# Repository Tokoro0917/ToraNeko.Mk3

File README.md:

# ToraNeko.Mk3

マイクロマウス（ハーフサイズクラス）ToraNeko の3代目機体（Mk3）のソフトウェア・ハードウェア（回路）・機構設計をまとめて管理するリポジトリです。
KOGUMA（クラシックサイズ機）とは別系譜の機体です。前身の KOGUMA.Mk3 系リポジトリはソフトウェアのみを対象としていましたが、本リポジトリでは
回路図・基板データ・配線資料なども含めて一元管理し、ソフトとハードの変更履歴を紐付けて追跡できるようにします。

ロボットの詳細な概要・仕様は [docs/overview.md](./docs/overview.md) を参照してください。
機体で選べるモードの一覧は [software/main-controller/README.md の「モード一覧」](software/main-controller/README.md#モード一覧今のファームウェアで選べるもの) にあります。

## ディレクトリ構成

```
.
├── software/    # マイコン・PC側ソフトウェア一式
├── hardware/    # 回路図・基板データ（KiCadプロジェクト）・BOM
├── mechanical/  # 機構部品・3Dモデル・図面
└── docs/        # 配線図、仕様書、設計メモ、議事録などのドキュメント
```

各ディレクトリの詳細は、それぞれの README.md を参照してください。

## 設計データの管理方針

- 回路・基板設計は [KiCad](https://www.kicad.org/) を使用します。プロジェクト一式は `hardware/kicad/` 以下にサブシステムごとのディレクトリを作って格納します。
- ソフトウェアは `software/` 以下にサブシステム・マイコンボードごとのディレクトリを作って格納します。
- 既存の KOGUMA.Mk3 のソフトウェア資産は、必要になったタイミングで個別に移行するかを検討します（現時点では未移行）。

## ライセンス

このリポジトリは [MIT License](./LICENSE) の下で公開されます。

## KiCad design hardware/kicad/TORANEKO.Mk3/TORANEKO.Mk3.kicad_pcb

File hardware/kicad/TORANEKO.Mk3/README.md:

# TORANEKO.Mk3

ToraNeko.Mk3 のメイン基板（1枚基板・全機能統合、基板一体型シャーシ）のKiCadプロジェクトです。

KiCadプロジェクト本体（`TORANEKO.Mk3.kicad_pro` / `.kicad_sch` / `.kicad_pcb`）を作成済みです（現状は空、これから回路図を起こしていきます）。
このディレクトリには、実際に回路図を起こす前に固めておいた機能ブロック構成・ペリフェラル割り当て案・BOMドラフトも一緒に置いています。

## 機能ブロック

| ブロック | 内容 |
|---|---|
| MCU | STM32F411CEU6 |
| モータドライバ | MP6551 × 2（左モータ用・右モータ用） |
| モータ | NFP-D0812-1-3.7（ブラシ付きDC）× 2 |
| エンコーダ | AS5047P（磁気式）× 2、磁石は左右のタイヤの軸（3×6 平行ピン）に取り付け |
| IMU | LSM6DSRXTR |
| 壁センサ | 反射型IR。受光: LTR-209、発光: OSI5FU3A11C、LEDドライバ: **NCR321PAS**（定電流・PWM対応）。前方斜め左右2組・側面左右2組の計4組 |
| 吸引ファン | サクションファン × 1（型番未定）。NチャネルMOSFETによるローサイドPWM駆動 |
| 電源 | 2セルLiPo入力 → MCU/センサ用3.3V系（**LXDC55FAAA-203**）、モータドライバ（MP6551）はLiPo直結 |
| デバッグ/書き込み | STLINK-V3MODS（SWD＋仮想COMポート）。USBは使わない |
| クロック | HSE 10MHz（セラミック発振子 CSTNE10M0G52Z000R0）→ SYSCLK 100MHz |

## ペリフェラル割り当て案（STM32F411CEU6）

正確なピン番号はKiCadで回路図を起こす際にデータシート（UFQFPN48パッケージ）で確定してください。
ここではどのペリフェラルをどのブロックに割り当てるかの方針のみ示します。

- **SPIバス（IMU・エンコーダ用）**: LSM6DSRXTR、AS5047P × 2 は共通SPIバス上にCS（チップセレクト）を分けて接続する案。SPIバスを分割するかは配線の都合で判断。
- **PWM（モータ駆動用）**: MP6551 × 2 に対し、1モータあたり2本（IN1/IN2、もしくはPWM+DIR）を想定。TIM1などの高機能タイマーを優先的に割り当てる。
- **ADC（壁センサ用）**: LTR-209（受光）× 4組ぶんでADC 4チャンネル（PA3〜PA6）を使用。OSI5FU3A11C（発光）側は **NCR321PAS**（LED 1個につき1個）の VEN を GPIO 2本で2組ずつ駆動する（組A: PB0、組B: PA7）
- **PWM（吸引ファン用）**: MOSFETゲート駆動用に1チャンネル。モータ駆動用タイマーとは別チャンネルを割り当てる。
- **UART（ログ出力）**: USART1（PA9 TX / PA10 RX）を STLINK-V3MODS の仮想COMポートに接続する案。USBは使わないので PA11/PA12 は他用途に使える。
- **SWD**: STLINK-V3MODS での書き込み・デバッグ用に PA13（SWDIO）/ PA14（SWCLK）/ NRST を確保。SWO（PB3）は任意。

## 電源設計メモ

- 入力: 2セルLiPo（7.4V公称、満充電8.4V程度）
- MCU/センサ系: 3.3Vへ降圧、**LXDC55FAAA-203** を使用
- 壁センサLEDドライバ（NCR321PAS）: **3.3V系から給電（決定）**。センサ周りにバッテリ電圧（変動する電圧）を持ち込まないため。LED 1個につき NCR321PAS 1個、**ピーク約 155mA** のパルス点灯。回路は下記「壁センサ発光回路」を参照
- モータ系: LiPoをレギュレータを介さず**MP6551に直結**（MP6551の定格電圧範囲内であることを確認済みとして進める）
- 吸引ファン系: LiPoから供給、MOSFETでPWM制御（レギュレータを挟むかはファン選定後に確定）

## 壁センサ発光回路

LED 1個につき NCR321PAS 1個（×4組）。発光制御の GPIO は2本で、1本の GPIO で2個の VEN を同時に駆動する（組A: PB0 → IC3/D7 と IC8/D9、組B: PA7 → IC4/D8 と IC9/D10）。組み合わせは **組A = 左前向き＋右向き、組B = 右前向き＋左向き**。横向きの2組は光軸が機体中央で交差する（クロス配置）が、別の組なので同時には点かない。同時に点く2組は向きが反対なので干渉しにくい。ただし同じ組の2個は機体の同じ側に並ぶ（右向きは左側に付いて右を向くため）ので、LED からの光が隣の受光素子に直接入らないよう、センサホルダで遮光する。

2個同時点灯なのでピーク電流は約 310mA（155mA × 2）。大容量コンデンサの電圧降下も2倍になり、NCR321PAS の電圧余裕は最悪で 1.4V をわずかに下回る見込み。足りない場合は電流が少し下がる（暗くなる）だけなので、実測で確認する。

```
【電源部：4組で共通】

 +3V3 ──[FB1]──┬──────────┬───────────── 3V3_LED（LED1〜4のアノードへ）
 (MCU系)        │          │
            C1,C2 ═╧═      C3 ═╧═ 0.1µF
         47µF×2 │          │
                 GND        GND

【発光部：1組分（×4組）】

 3V3_LED
    │
    ▼  D1  OSI5FU3A11C（1: アノード、2: カソード）
    │
  ┌─┴──────────────── U1 NCR321PAS ──┐
  │  6: IOUT / 7: IOUT（裏面パッド）  │
  │  1: VEN ◄───────┬──────── GPIO（組A: PB0 / 組B: PA7、1本で2個の VEN を駆動）
  │                R2 100kΩ           │
  │                 │                 │
  │                GND                │
  │  2: REXT ──[R1 5.1Ω 1%]── GND     │
  │  5: GND ───────────────── GND     │
  │  3, 4, 8: N/C                     │
  └───────────────────────────────────┘
```

| 記号 | 部品 | 値 | 数 | 備考 |
|---|---|---|---|---|
| D1 | 赤外LED | OSI5FU3A11C | 4 | 940nm。IF=100mA で VF typ 1.35V / max 1.6V。パルス最大 1000mA（100µs, 1/100） |
| U1 | 定電流ドライバ | NCR321PAS | 4 | DFN2020D-6 |
| R1 | Rext | 5.1Ω 1% | 4 | 約 155mA（データシート Fig.16/17 の 4Ω≒190mA、6Ω≒135mA から 1/Rext で補間）。E96 の 4.99Ω なら約 160mA。センサごとに差し替え可能なよう 0603/0805 |
| R2 | VEN プルダウン | 100kΩ | 4 | リセット中（GPIO 入力状態）に LED が点かないようにする |
| FB1 | フェライトビーズ | 0603、定格 300mA 以上、DCR 0.1Ω 以下 | 1 | 0Ω でも可。MCU・ADC 側の 3.3V にパルス電流を流さないため |
| C1, C2 | バルクコンデンサ | 47µF 10V X5R 1206 | 2 | DC バイアス込みで実効 100µF 程度を確保。ドライバ直近 |
| C3 | デカップリング | 0.1µF | 1 | ドライバ直近。4組が離れる場合は各ドライバに追加 |

### 設計上の注意

- **VEN は GPIO から直結**（直列抵抗を入れない）。EN 電圧で出力電流が変わる（Fig.24）ため。VEN の絶対最大定格は 4.5V
- **NCR321PAS の裏面パッド（7ピン）は IOUT。GND ではない。** GND ベタにつなぐと LED が常時点灯になる。LED カソードと同じネットにし、放熱用に銅箔を確保する
- 電圧余裕（155mA 時の見積り）: 3.3V − C1,C2 電圧降下（約 31mV: 155mA × 20µs / 100µF）− FB1（約 16mV）− VF（推定 typ 1.65V / 最悪 1.8V）= **typ 約 1.6V / 最悪 約 1.45V**。NCR321PAS の最小オーバーヘッド 1.4V を満たす（180mA〔4.3Ω〕だと最悪で約 1.4V とぎりぎりになるため、安定性を優先して 5.1Ω とした）
  - このため **1回の点灯時間は 10〜20µs** を目安にする（ソフト側で調整）
  - 余裕が足りない場合は電流が設定値より下がる（暗くなる）だけで、壊れはしない。ただし明るさが温度で変わりやすくなる
- パルス電流のループ（C1,C2 → LED → U1 → R1 → GND → C1,C2）を小さくし、受光側・ADC 入力の近くを通さない
- 側面センサは壁が近く、受光側が飽和する可能性がある。実測で距離と AD 値の関係を確認し、必要ならセンサごとに Rext を変える（例: 側面は 9.1Ω≒100mA）

## 部品配置ガイド（DXF）

機体全体の STEP（`mechanical/exported/TORANEKO.Mk3_v36.step`）から、配置の目安になる DXF を生成したもの。KiCad の PCB エディタで「ファイル → インポート → グラフィック」から `User.Drawings` などのレイヤーに読み込み、ガイド内の基板外形（レイヤー `00_BOARD`）が既存の Edge.Cuts に重なるように置く。

### `配置ガイド_メイン基板.dxf`（上から見た図。`メイン基板外形.dxf` と同じ座標系）

| レイヤー | 内容 |
|---|---|
| `00_BOARD` | メイン基板外形（位置合わせ用） |
| `10_ENC_BOARD` | エンコーダ基板が立つ位置（6 × 0.6mm）と中心線 |
| `11_ENC_CHIP` | AS5047P の位置（エンコーダ基板の外側＝磁石側の面） |
| `12_MAGNET_AXIS` | 磁石（Φ3）と回転軸の線 |
| `20_CONTACT` | 基板面（z=0.65mm）で切った断面＝基板に接する部品の足元（モータマウント、センサホルダ、支柱、ホイール、41T ギア） |
| `30_OVERHANG` | 基板の上に浮いている部品の外形（破線）。ラベルの値は基板上面からの隙間＝その下に置ける部品の高さの上限 |

基板上面からの隙間（この高さ未満の部品なら下に置ける）:

| 部品 | 隙間 |
|---|---|
| モータ NFP-D0812 | 1.25mm |
| ベアリング LF-630 | 1.01mm |
| 吸引ファンモータ MK06-45 | 2.00mm |
| 平行ピン 3×6 / 磁石 | 3.11mm |
| ピニオン 11T | 3.36mm |
| 吸引ファンモータマウント | 4.98mm |

### エンコーダ基板の位置（KiCad 座標）

現在のメイン基板外形の取り込み位置（DXF 原点 → KiCad (96.5, 61.05)）で換算した値。

| | エンコーダ基板が立つ範囲 | 中心 | AS5047P（チップ）がある側 | 磁石 |
|---|---|---|---|---|
| 右（機体右、非ミラー側） | X 118.257〜118.857、Y 63.05〜69.05 | (118.557, 66.05) | +X 側（X 118.81〜120.00） | X 120.5〜121.5 |
| 左（機体左、ミラー側） | X 100.943〜101.543、Y 63.05〜69.05 | (101.243, 66.05) | −X 側（X 99.80〜100.99） | X 98.3〜99.3 |

- 磁石の回転軸は Y = 66.05、メイン基板上面から高さ 4.61mm
- エンコーダ基板は高さ 8.5mm、厚さ 0.6mm（STEP 上）。AS5047P と磁石の隙間は 0.5mm

### `配置ガイド_エンコーダ基板.dxf`（エンコーダ基板を磁石側から見た図。`エンコーダ外形.dxf` と同じ座標系）

- 上端（y = 0.513）がメイン基板にはんだ付けされる辺
- 磁石の軸（Φ1 の円）はメイン基板から 4.61mm。AS5047P はこの軸に中心を合わせ、フットプリントを 90° 回して置く（ピンの列が上下に来る向き）
- AS5047P のパッドから基板端までは、メイン基板側 0.94mm、反対側 0.21mm（反対側は製造ルールの最小クリアランスを要確認）
- `30_EDGE_PAD_ZONE`: メイン基板とはんだ付けするエッジパッドを置ける範囲。裏面（チップのない面）は幅いっぱいに 0.79mm、チップ面は同じ 0.79mm の帯か、左右の角（0.68 × 1.3mm）

## エンコーダ接続用フットプリント（`TORANEKO_Encoder.pretty/`）

エンコーダ基板（6 × 8.5 × 0.6mm）をメイン基板に垂直に立て、はんだで接続するためのフットプリント。左右のエンコーダ基板は同じ設計のまま使える（180° 回して置くだけ）。

| フットプリント | 使う部品 | 原点 | パッド |
|---|---|---|---|
| `TN_ENC_Edge` | エンコーダ基板側（U3, U5） | はんだ付けする辺の中央。+Y が基板の奥（メイン基板から離れる向き） | 1〜4（MOSI, MISO, SCK, CS）: 裏面、幅 0.9mm、ピッチ 1.4mm、辺から 0.2〜1.2mm。5〜6（VCC, GND）: チップ面、幅 2.0mm、辺から 0.2〜0.72mm（AS5047P のパッドと 0.2mm 以上離す） |
| `TN_ENC_Base` | メイン基板側（U4, U6） | エンコーダ基板が立つ位置の中央。−Y がチップ側 | 1〜4: 裏面側の列、5〜6: チップ側の列。エンコーダ基板の面（中心から ±0.3mm）から外へ 1.0mm |

- `TN_ENC_Edge` の `Dwgs.User` に、磁石の軸（辺から 4.613mm）と AS5047P の外形（5.0 × 4.4mm）を描いてある。AS5047P はその中心に合わせ、90° 回して置く
- `TN_ENC_Base` の置き方（回転は KiCad の角度）:

| | 位置 | 回転 |
|---|---|---|
| 右エンコーダ（U4 か U6、チップが +X 向き） | (118.557, 66.05) | 270° |
| 左エンコーダ（チップが −X 向き） | (101.243, 66.05) | 90° |

- エンコーダ基板は小さいため、基板端クリアランス（基板のセットアップ → 制約 → 銅箔から基板端）は **0.2mm** にする（0.5mm だと AS5047P のパッドとエッジパッドが違反になる。AS5047P のパッドは上端から 0.22mm）
- ライブラリの追加: 設定 → フットプリントライブラリの管理 → プロジェクト固有のライブラリ に `${KIPRJMOD}/TORANEKO_Encoder.pretty` を追加

## TODO

- [x] SPIバスの分割方針 → IMU は SPI1（PB3/4/5）、エンコーダは SPI2（PB13/14/15）に分割
- [x] モータPWM用タイマー・チャンネルの確定 → TIM4 CH1〜CH4（PB6〜PB9）
- [ ] NCR321PASの電流設定抵抗値の実測確認: **Rext = 5.1Ω（1%、約 155mA）** に決定。実機で電流・IOUT 電圧（1.2V 以上残っているか）・温度による AD 値の変化を確認
- [ ] NCR321PASの3.3V系での電圧マージン実測確認（155mA 時の見積りは typ 約1.6V / 最悪 約1.45V。OSI5FU3A11C の 155mA 時 VF はデータシートに記載がないため実測が必要）
- [ ] LXDC55FAAA-203 の出力電流に LED パルス分（最大約 155mA、同時点灯1個）の余裕があるか確認
- [ ] 吸引ファンの型番選定
- [ ] 吸引ファン用MOSFET・ゲート抵抗・フライホイールダイオードの選定
- [ ] 吸引ファンの電源系統（LiPo直結か別レギュレータか）の判断
- [x] 正式なピンアサイン表の作成 → `software/main-controller/PIN_REQUIREMENTS.md`（回路図 `9a54a18` から抽出）
- [ ] 各部品のシンボル・フットプリントをライブラリに追加し、回路図に配置

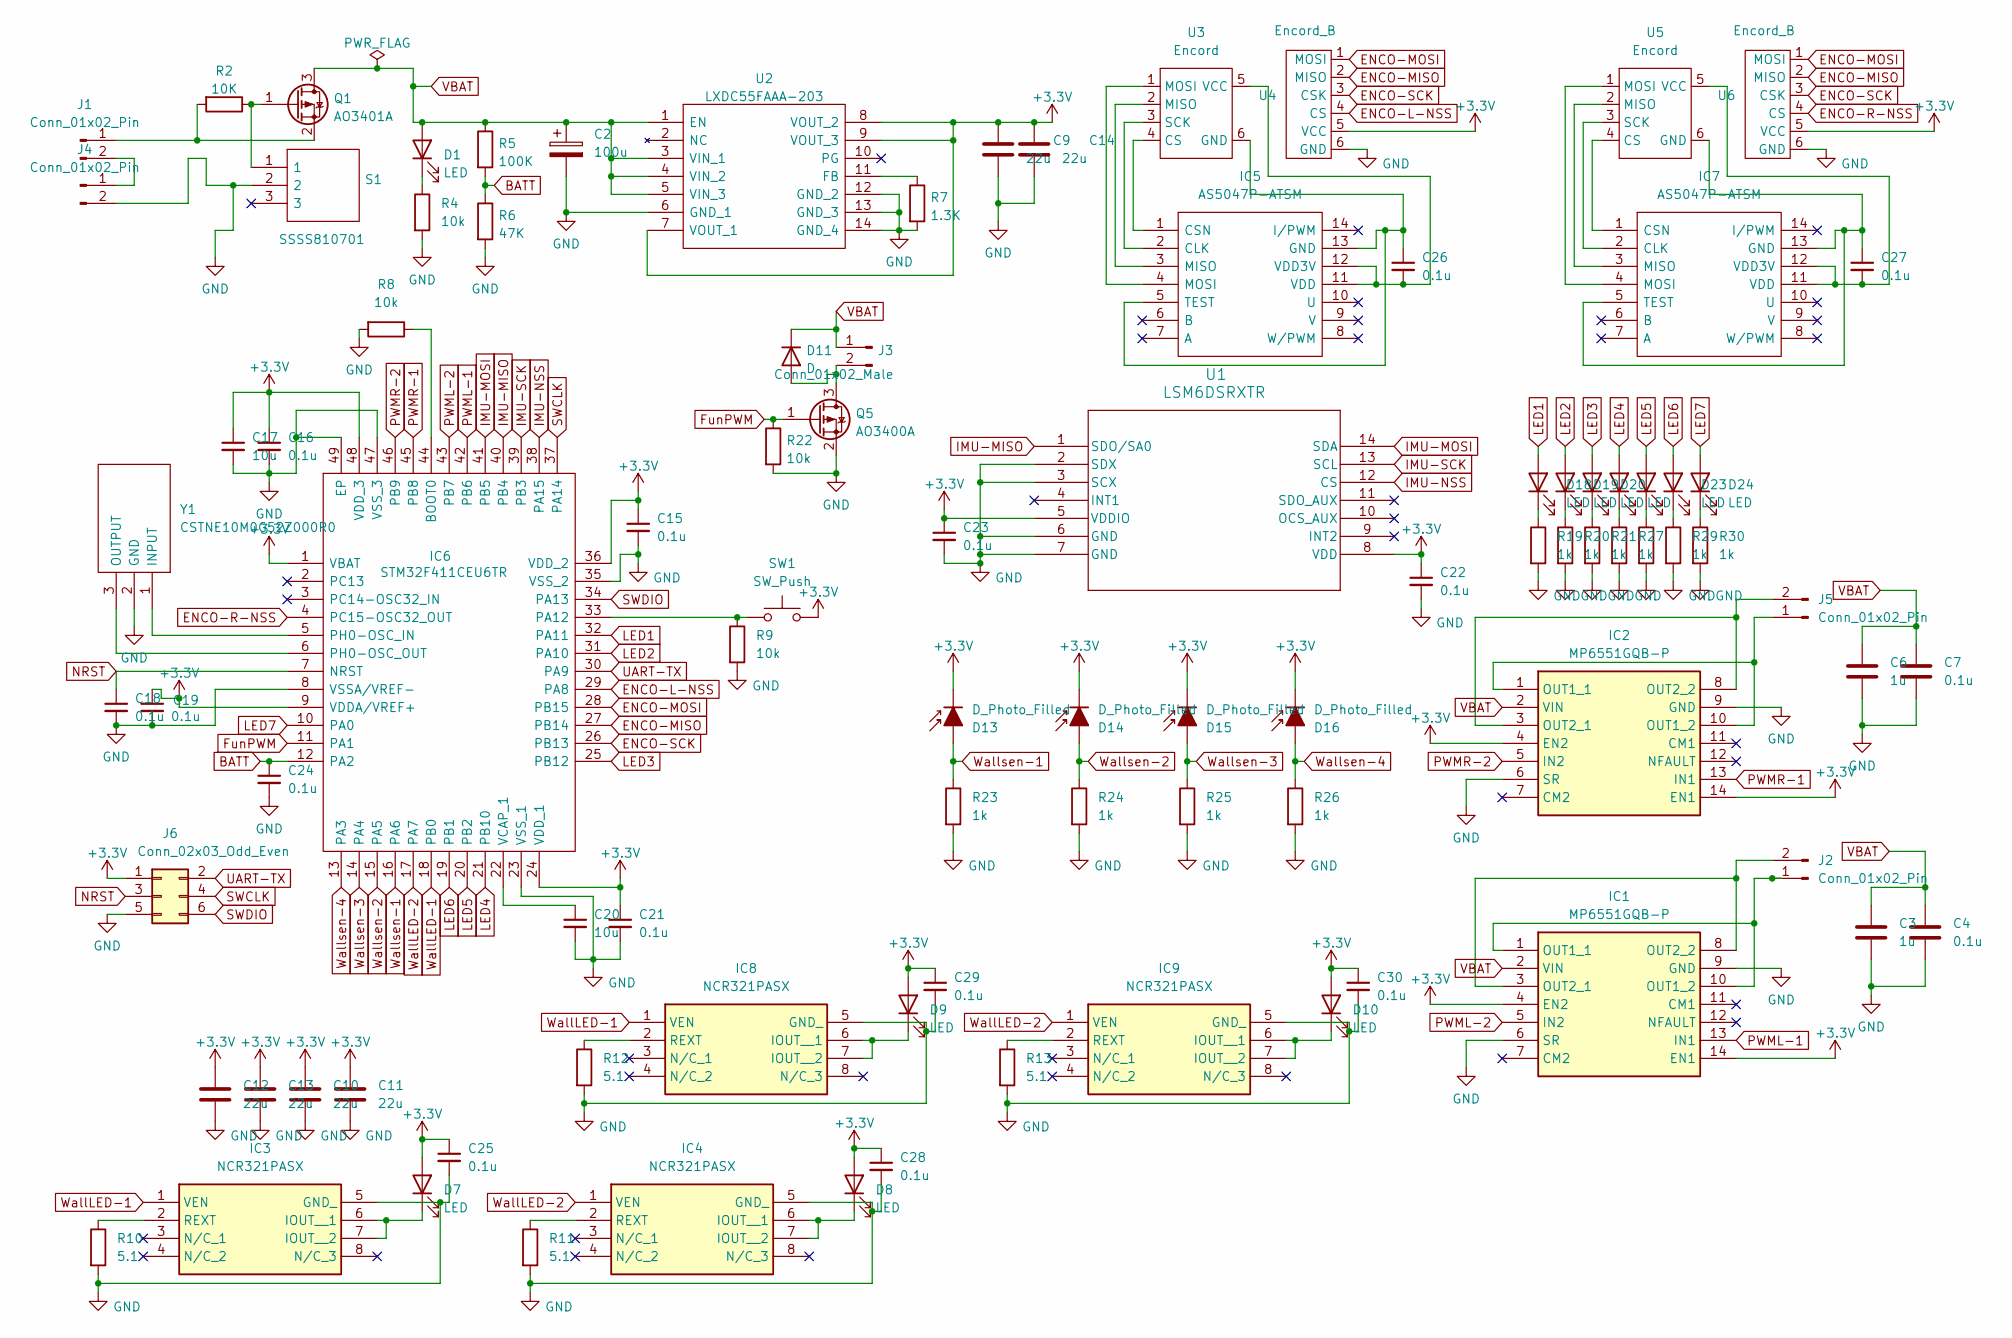
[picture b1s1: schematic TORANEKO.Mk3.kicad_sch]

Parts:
C2: 100u; CP_Elec_6.3x5.4
C3, C6: 1u; C_0402_1005Metric
C4, C7, C15, C16, C18, C19, C21, C22, C23, C24, C25, C26, C27, C28, C29, C30: 0.1u; C_0402_1005Metric
C9, C10, C11, C12, C13, C14: 22u; C_0603_1608Metric
C17, C20: 10u; C_0402_1005Metric
D1, D18, D19, D20, D21, D22, D23, D24: LED; LED_0402_1005Metric
D7, D8, D9, D10: LED; LED_D3.0mm
D11: D; D_SOD-123F
D13, D14, D15, D16: D_Photo_Filled; LED_D3.0mm
IC1, IC2: MP6551GQB-P; MP6551GQBP; Manufacturer_Part_Number MP6551GQB-P
IC3, IC4, IC8, IC9: NCR321PASX; Manufacturer_Part_Number NCR321PASX
IC5, IC7: AS5047P-ATSM; SOP65P640X120-14N; Manufacturer_Part_Number AS5047P-ATSM
IC6: STM32F411CEU6TR; QFN50P700X700X60-49N-D; Manufacturer_Part_Number STM32F411CEU6TR
J1, J4: Conn_01x02_Pin; JST_ZH_B2B-ZR_1x02_P1.50mm_Vertical
J2, J5: Conn_01x02_Pin; C_0805_2012Metric
J3: Conn_01x02_Male; C_0805_2012Metric
J6: Conn_02x03_Odd_Even; PinHeader_2x03_P1.27mm_Vertical
Q1: AO3401A; SOT-23
Q5: AO3400A; SOT-23
R2: 10K; R_0402_1005Metric
R4, R8, R9, R22: 10k; R_0402_1005Metric
R5: 100K; R_0402_1005Metric
R6: 47K; R_0402_1005Metric
R7: 1.3K; R_0402_1005Metric
R10, R11, R12, R13: 5.1; R_0402_1005Metric
R19, R20, R21, R23, R24, R25, R26, R27, R28, R29, R30: 1k; R_0402_1005Metric
S1: SSSS810701; Manufacturer_Part_Number SSSS810701
SW1: SW_Push; SW_Push_SPST_NO_Alps_SKRK
U1: LSM6DSRXTR; LGA-14L_STM
U2: LXDC55FAAA-203; LXDC55FAAA203; Manufacturer_Part_Number LXDC55FAAA-203
U3, U5: Encord; TN_ENC_Edge
U4, U6: Encord_B; TN_ENC_Base
Y1: CSTNE10M0G52Z000R0; Manufacturer_Part_Number CSTNE10M0G52Z000R0

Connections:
+3.3V: C9.1, C10.1, C11.1, C12.1, C13.1, C14.1, C15.1, C16.1, C17.1, C19.1, C21.1, C22.1, C23.1, C25.1, C28.1, C29.1, C30.1, D7.2 (A), D8.2 (A), D9.2 (A), D10.2 (A), D13.1 (K), D14.1 (K), D15.1 (K), D16.1 (K), IC1.4 (EN2), IC1.14 (EN1), IC2.4 (EN2), IC2.14 (EN1), IC6.1 (VBAT), IC6.9 (VDDA/VREF+), IC6.24 (VDD_1), IC6.36 (VDD_2), IC6.48 (VDD_3), J6.1, SW1.2, U1.5 (VDDIO), U1.8 (VDD), U2.7 (VOUT_1), U2.8 (VOUT_2), U2.9 (VOUT_3), U4.5 (VCC), U6.5 (VCC)
BATT: C24.1, IC6.12 (PA2), R5.2, R6.1
ENCO-L-NSS: IC6.29 (PA8), U4.4 (CS)
ENCO-MISO: IC6.27 (PB14), U4.2 (MISO), U6.2 (MISO)
ENCO-MOSI: IC6.28 (PB15), U4.1 (MOSI), U6.1 (MOSI)
ENCO-R-NSS: IC6.4 (PC15-OSC32_OUT), U6.4 (CS)
ENCO-SCK: IC6.26 (PB13), U4.3 (CSK), U6.3 (CSK)
FunPWM: IC6.11 (PA1), Q5.1 (G), R22.1
GND: C2.2, C3.2, C4.2, C6.2, C7.2, C9.2, C10.2, C11.2, C12.2, C13.2, C14.2, C15.2, C16.2, C17.2, C18.2, C19.2, C20.2, C21.2, C22.2, C23.2, C24.2, C25.2, C28.2, C29.2, C30.2, IC1.6 (SR), IC1.9 (GND), IC2.6 (SR), IC2.9 (GND), IC3.5 (GND_), IC4.5 (GND_), IC6.8 (VSSA/VREF-), IC6.23 (VSS_1), IC6.35 (VSS_2), IC6.47 (VSS_3), IC6.49 (EP), IC8.5 (GND_), IC9.5 (GND_), J4.2, J6.5, Q5.2 (S), R4.2, R6.2, R7.2, R8.2, R9.2, R10.2, R11.2, R12.2, R13.2, R19.2, R20.2, R21.2, R22.2, R23.2, R24.2, R25.2, R26.2, R27.2, R28.2, R29.2, R30.2, S1.2, U1.2 (SDX), U1.3 (SCX), U1.6 (GND), U1.7 (GND), U2.6 (GND_1), U2.12 (GND_2), U2.13 (GND_3), U2.14 (GND_4), U4.6 (GND), U6.6 (GND), Y1.2 (GND)
IMU-MISO: IC6.40 (PB4), U1.1 (SDO/SA0)
IMU-MOSI: IC6.41 (PB5), U1.14 (SDA)
IMU-NSS: IC6.38 (PA15), U1.12 (CS)
IMU-SCK: IC6.39 (PB3), U1.13 (SCL)
LED1: D18.2 (A), IC6.32 (PA11)
LED2: D19.2 (A), IC6.31 (PA10)
LED3: D20.2 (A), IC6.25 (PB12)
LED4: D21.2 (A), IC6.21 (PB10)
LED5: D22.2 (A), IC6.20 (PB2)
LED6: D23.2 (A), IC6.19 (PB1)
LED7: D24.2 (A), IC6.10 (PA0)
NRST: C18.1, IC6.7 (NRST), J6.3
unnamed: D1.1 (K), R4.1
unnamed: D7.1 (K), IC3.6 (IOUT__1), IC3.7 (IOUT__2)
unnamed: D8.1 (K), IC4.6 (IOUT__1), IC4.7 (IOUT__2)
unnamed: D9.1 (K), IC8.6 (IOUT__1), IC8.7 (IOUT__2)
unnamed: D10.1 (K), IC9.6 (IOUT__1), IC9.7 (IOUT__2)
unnamed: D11.2 (A), J3.2, Q5.3 (D)
unnamed: D18.1 (K), R19.1
unnamed: D19.1 (K), R20.1
unnamed: D20.1 (K), R21.1
unnamed: D21.1 (K), R27.1
unnamed: D22.1 (K), R28.1
unnamed: D23.1 (K), R29.1
unnamed: D24.1 (K), R30.1
unnamed: IC1.1 (OUT1_1), IC1.10 (OUT1_2), J2.1
unnamed: IC1.3 (OUT2_1), IC1.8 (OUT2_2), J2.2
unnamed: IC2.1 (OUT1_1), IC2.10 (OUT1_2), J5.1
unnamed: IC2.3 (OUT2_1), IC2.8 (OUT2_2), J5.2
unnamed: IC3.2 (REXT), R10.1
unnamed: IC4.2 (REXT), R11.1
unnamed: IC5.2 (CLK), U3.3 (SCK)
unnamed: IC5.1 (CSN), U3.4 (CS)
unnamed: C26.1, IC5.5 (TEST), IC5.13 (GND), U3.6 (GND)
unnamed: IC5.3 (MISO), U3.2 (MISO)
unnamed: IC5.4 (MOSI), U3.1 (MOSI)
unnamed: C26.2, IC5.11 (VDD), IC5.12 (VDD3V), U3.5 (VCC)
unnamed: IC6.44 (BOOT0), R8.1
unnamed: IC6.33 (PA12), R9.1, SW1.1
unnamed: IC6.5 (PH0-OSC_IN), Y1.1 (INPUT)
unnamed: IC6.6 (PH0-OSC_OUT), Y1.3 (OUTPUT)
unnamed: C20.1, IC6.22 (VCAP_1)
unnamed: IC7.2 (CLK), U5.3 (SCK)
unnamed: IC7.1 (CSN), U5.4 (CS)
unnamed: C27.1, IC7.5 (TEST), IC7.13 (GND), U5.6 (GND)
unnamed: IC7.3 (MISO), U5.2 (MISO)
unnamed: IC7.4 (MOSI), U5.1 (MOSI)
unnamed: C27.2, IC7.11 (VDD), IC7.12 (VDD3V), U5.5 (VCC)
unnamed: IC8.2 (REXT), R12.1
unnamed: IC9.2 (REXT), R13.1
unnamed: J1.1, Q1.2 (S), R2.2
unnamed: J1.2, J4.1
unnamed: Q1.1 (G), R2.1, S1.1
unnamed: R7.1, U2.11 (FB)
PWML-1: IC1.13 (IN1), IC6.42 (PB6)
PWML-2: IC1.5 (IN2), IC6.43 (PB7)
PWMR-1: IC2.13 (IN1), IC6.45 (PB8)
PWMR-2: IC2.5 (IN2), IC6.46 (PB9)
SWCLK: IC6.37 (PA14), J6.4
SWDIO: IC6.34 (PA13), J6.6
UART-TX: IC6.30 (PA9), J6.2
VBAT: C2.1, C3.1, C4.1, C6.1, C7.1, D1.2 (A), D11.1 (K), IC1.2 (VIN), IC2.2 (VIN), J3.1, Q1.3 (D), R5.1, U2.1 (EN), U2.3 (VIN_1), U2.4 (VIN_2), U2.5 (VIN_3)
WallLED-1: IC3.1 (VEN), IC6.18 (PB0), IC8.1 (VEN)
WallLED-2: IC4.1 (VEN), IC6.17 (PA7), IC9.1 (VEN)
Wallsen-1: D13.2 (A), IC6.16 (PA6), R23.1
Wallsen-2: D14.2 (A), IC6.15 (PA5), R24.1
Wallsen-3: D15.2 (A), IC6.14 (PA4), R25.1
Wallsen-4: D16.2 (A), IC6.13 (PA3), R26.1

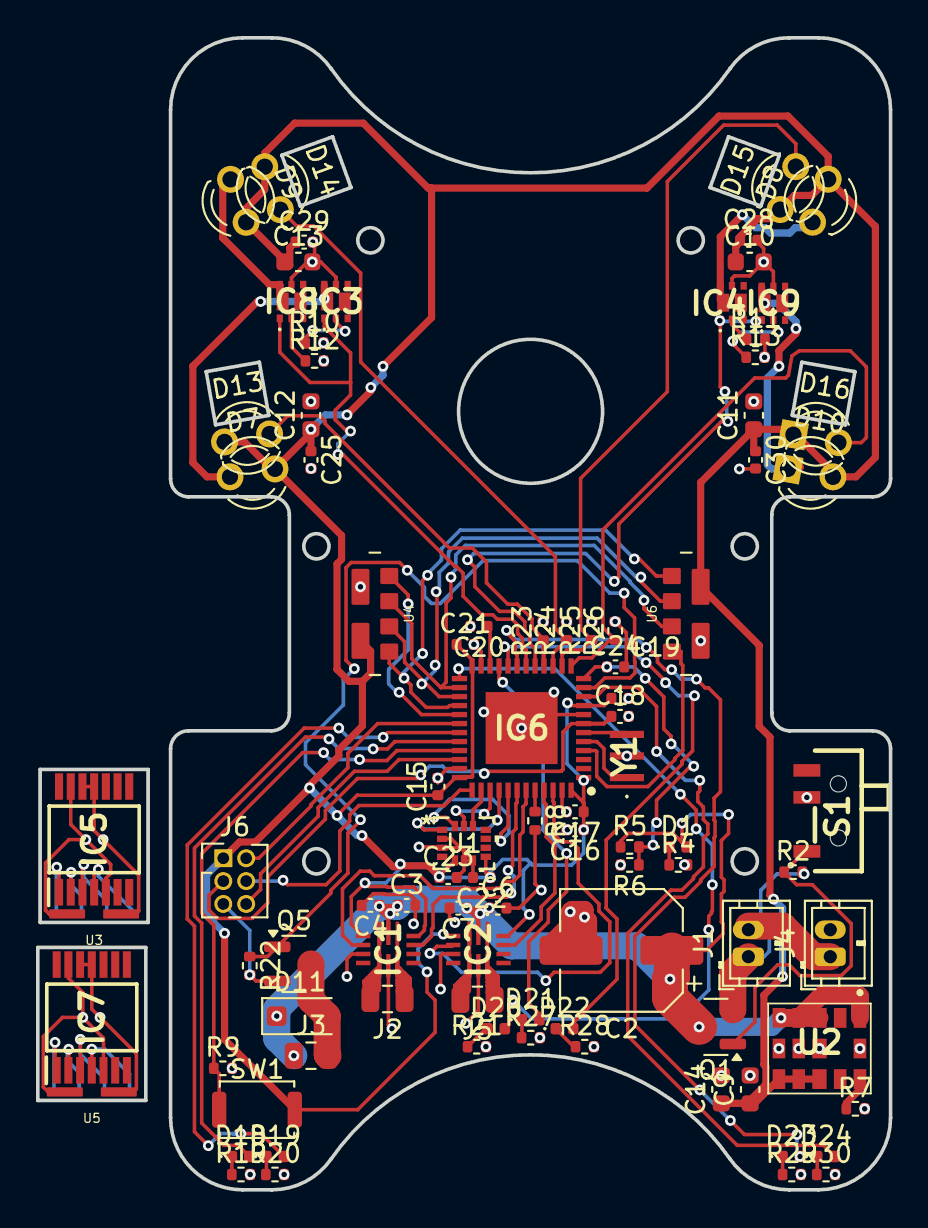
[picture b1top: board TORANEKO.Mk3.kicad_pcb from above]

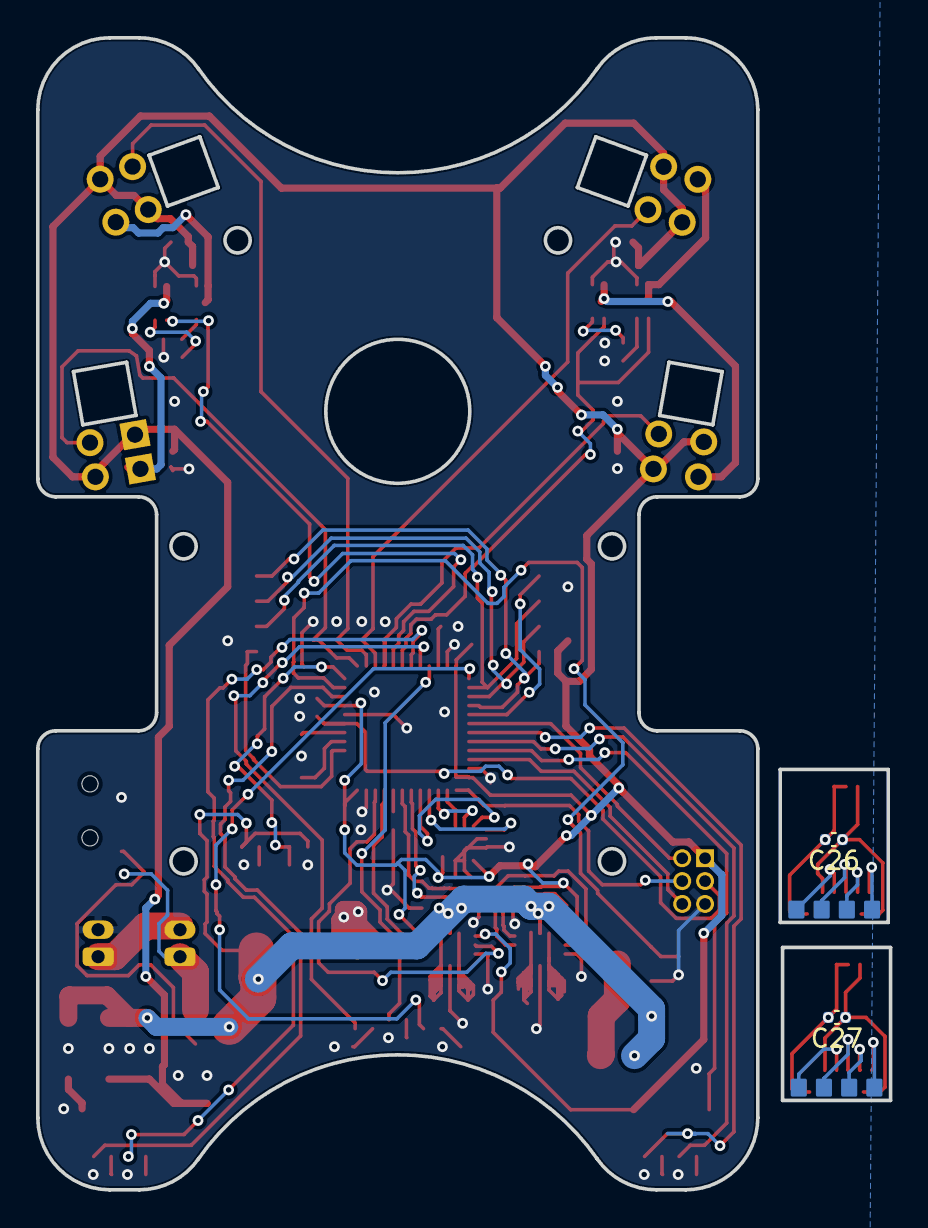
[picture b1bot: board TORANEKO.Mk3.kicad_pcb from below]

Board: 2 copper layers, 40.0 x 64.0 mm, 93 parts (2 on the bottom side), 77 nets.

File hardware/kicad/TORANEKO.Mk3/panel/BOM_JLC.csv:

Comment,Designator,Footprint,LCSC Part #
100nF 16V X7R 0402,"C4,C7,C15,C16,C18,C19,C21,C22,C23,C24,C25,C28,C29,C30",0402,C1525
10uF 6.3V X5R 0402,"C17,C20",0402,C15525
1uF 25V X5R 0402,"C3,C6",0402,C52923
22uF 6.3V X5R 0603,"C9,C10,C11,C12,C13,C14",0603,C59461
5.1R 1% 0402,"R10,R11,R12,R13",0402,C137955
47k 1% 0402,R6,0402,C25792
10k 1% 0402,"R2,R4,R8,R9,R22",0402,C25744
2k 1% 0402,"R19,R20,R21,R27,R28,R29,R30",0402,C4109
1k 1% 0402,"R23,R24,R25,R26",0402,C11702
100k 1% 0402,R5,0402,C25741
1.3k 1% 0402,R7,0402,C25866
LED Blue 0402,"D1,D18,D19,D20,D21,D22,D23,D24",0402,C130724
AO3401A P-MOSFET,Q1,SOT-23,C15127
AO3400A N-MOSFET,Q5,SOT-23,C20917
STM32F411CEU6,IC6,UFQFPN-48,C60420
LSM6DSRXTR,U1,LGA-14,C2970339
MP6551GQB-Z,"IC1,IC2",QFN-14 2.5x3,C3681210
NCR321PASX,"IC3,IC4,IC8,IC9",DFN2020-6,C3190647

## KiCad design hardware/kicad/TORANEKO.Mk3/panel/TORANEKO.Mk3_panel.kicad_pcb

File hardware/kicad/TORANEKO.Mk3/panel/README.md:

# 発注用パネル

> **発注記録（2026-10）**: メイン基板は 1 枚のデータで出し、レールとフィデューシャルは JLCPCB に付けてもらった（このフォルダのメイン基板パネルは未使用）。PCBA は 3 台、状態表示 LED は青（C130724）＋ 2kΩ。エンコーダ基板＋上部固定基板はこのフォルダのパネルで基板のみ。

発注は 2 つ。同じカートに入れれば 1 回で発注・発送できる。

| 注文 | ファイル | PCBA |
|---|---|---|
| メイン基板 | `TORANEKO.Mk3_main_panel.kicad_pcb`（下記「メイン基板パネル」） | Standard PCBA（抵抗・コンデンサ・IC など 65 個） |
| エンコーダ基板 ×6 ＋ 上部固定基板 | `TORANEKO.Mk3_panel.kicad_pcb` | なし（C26・C27 は手はんだ） |

## エンコーダ基板 ×6 ＋ 上部固定基板 ×1

エンコーダ基板（6 × 8.5 × 0.6mm）6 枚（IC5 側 ×3、IC7 側 ×3）と、上部固定基板（25.75 × 26.8 × 0.6mm、銅箔なし）1 枚を並べた発注用パネル。メイン基板とは別の注文で出す。

| 項目 | 値 |
|---|---|
| パネル寸法 | 60 × 56.3mm（枠 5mm、基板間・枠との隙間 2mm、上下の段の間に幅 3mm の桟） |
| ミシン目 | NPTH Φ0.5mm、ピッチ 0.75mm、1 か所 3 穴。穴は基板の外側（タブ側）に置き、折ったあとの残りは基板の外に出る |

## エンコーダ基板（上の段）

| 項目 | 値 |
|---|---|
| 基板の固定 | 左右の辺のタブ（上端から 0.5〜2.5mm、幅 2mm）＋ミシン目 |
| はんだ付けする辺（下辺） | タブなし。ルーターで切るのできれいな辺になる |
| 上辺 | タブなし（AS5047P のパッドまで 0.22mm しかないため） |

- ミシン目の穴から銅箔までは 0.8mm 以上
- パネル内の各コピーは別のネット名（`_2`, `_3` 付き）にしてあるので、DRC で「未接続」は出ない

## 上部固定基板（下の段）

| 項目 | 値 |
|---|---|
| 外形 | `../上部固定基板外形.dxf` から読み込み（円弧は 2µm 以下の誤差で折れ線にしている） |
| 基板の固定 | まっすぐな辺だけにタブ（幅 2mm）: 左辺 ×2、上下の短い直線辺 ×1 ずつ。曲線の辺にはタブを付けない |
| 内側の抜き | 3 か所の抜きと Φ6.1 の穴は Edge.Cuts、Φ1.4 の穴 ×6 は NPTH |
| ロゴ | `../ロゴ_ホワイトグリント.dxf` を F.SilkS に塗りつぶしで配置（左下の空き、右に 90° 回転、幅 8.0mm）。外形・抜き・穴から 0.3mm 離して入る最大の大きさをスクリプトが自動で決める |

- DXF（y 上向き）を KiCad（y 下向き）に変換しているので、パネル上では DXF を上下反転した向きになる。銅箔のない板なので、裏返せば同じ形
- ロゴは 8mm と小さいため、線の 1 割ほどがシルクの最小線幅（0.15mm）より細い。細い先端や線の間の隙間は、印刷でつぶれたり欠けたりすることがある
- 左辺のタブの跡（ミシン目のバリ）が組み付けに当たる場合は、やすりで落とす

## 作り直し方

メイン基板（`../TORANEKO.Mk3.kicad_pcb`）のエンコーダ部分や `../上部固定基板外形.dxf` を修正したら、次で作り直す。

```bash
python3 make_panel.py
```

- 必要なライブラリ: `shapely`、`ezdxf`
- メイン基板上でエンコーダ基板を移動した場合も、`BOARDS` の外形の座標を直す（部品の相対位置が同じなら他は不要）
- エンコーダ基板の外形の位置（スクリプト内の `BOARDS`）が変わった場合は、そこも直す
- 上部固定基板の上下のタブ位置は、DXF の直線辺（x = -7.25〜0.13）の中央に決め打ちしている。外形を変えたらスクリプトの `utab_x0` を確認する

## 発注時の設定（JLCPCB の例）

- Panel by Customer（自分で面付け済み）、V-Cut なし
- 厚さ 0.6mm、2 層
- ガーバーは KiCad でこのファイルを開いて出力する

## メイン基板パネル（PCBA 用）

0.6mm 厚は JLCPCB の Economic PCBA（0.8〜1.6mm）に対応していないため、Standard PCBA で出す。
Standard PCBA は 70×70mm 以上・レール・フィデューシャルが必要なので、メイン基板 1 枚に枠を付けた。

| 項目 | 値 |
|---|---|
| パネル寸法 | 70 × 78mm（左右のレール 13mm、上下 5mm、基板との隙間 2mm） |
| タブ | 左右のまっすぐな辺に 2 か所ずつ（幅 2.5mm、ミシン目 NPTH Φ0.5 × 3）。タイヤ用の切り欠きと前後の曲線には付けない |
| フィデューシャル | 3 個（Φ1mm の銅、マスク開口 Φ2mm）、左右のレール |
| ツーリングホール | 4 個（NPTH Φ1.152）、レールの角 |

- タブの位置は、銅箔から 0.6mm 以上・部品のコートヤードから 1.8mm 以上離れた所を選んでいる（`make_main_panel.py` の `TABS`）。辺の近くの部品を動かしたら確認する
- パネルではメイン基板の Eco1.User / Dwgs.User の図形（配置ガイド）は省いている
- KiCad で開いたら GND ベタを塗り直す（B キー）。DRC 用のルールは `TORANEKO.Mk3_main_panel.kicad_dru`（メイン基板と同じ内容）

### PCBA の部品（`BOM_JLC.csv` / `CPL_JLC.csv`）

`make_jlc_files.py` の `PARTS` に書いた部品だけを実装する（18 種類 65 個）。IC6（STM32）・U1（LSM6DSRX）・IC1/IC2（MP6551）・IC3/IC4/IC8/IC9（NCR321PAS）も裏面パッドや LGA で手はんだが難しいため含める。MP6551 は JLCPCB にある -Z 品（回路図は -P）。C3・C6（VBAT）は 0402 で 16V 以上の 10µF がないため 1µF 25V に変更（VBAT には C2 100µF もある）。LCSC 番号は 2026-10 に JLCPCB の部品検索で在庫を確認したもの。

| 手はんだにする部品 | 理由 |
|---|---|
| U2（LXDC55FAAA-203） | JLCPCB で扱いなし |
| C2（100µF 16V 電解 6.3×5.4）、D11（ショットキー、SOD-123F） | 大きくて手はんだしやすい部品なので段取り費（1 種類 $1.5）を省く。D11 は秋月の SS2040FL（40V 2A、SOD-123FL、通販コード 102073）が使える |
| Y1（CSTNE10M0G52Z000R0）、SW1（SKRKAEE010） | JLCPCB に在庫なし |
| J1〜J6、S1、THT の LED/受光素子（D7〜D10, D13〜D16） | コネクタ・スイッチ・THT |

### 作り直しと発注の手順

```bash
python3 make_main_panel.py   # メイン基板を直したら作り直す
python3 make_jlc_files.py    # BOM_JLC.csv と CPL_JLC.csv
```

1. KiCad で `TORANEKO.Mk3_main_panel.kicad_pcb` を開き、ベタを塗り直して DRC
2. ガーバーとドリルを出力（原点はデフォルトのまま）
3. JLCPCB: 厚さ 0.6mm、Panel by Customer、PCB Assembly → **Standard**、Top side
4. BOM に `BOM_JLC.csv`、CPL に `CPL_JLC.csv` を指定
5. 部品の向き（IC の 1 番ピン・LED・ダイオード・電解コンデンサ・MOSFET）を JLCPCB のプレビューで必ず確認する。特に自作ライブラリの IC（IC6, U1, IC1〜IC4, IC8, IC9）は JLCPCB 側の向きとずれることがある
6. IC は在庫が少ない（2026-10 時点で LSM6DSRX 50 個、MP6551 11 個、NCR321PAS 80 個）ので、発注前に在庫を確認する

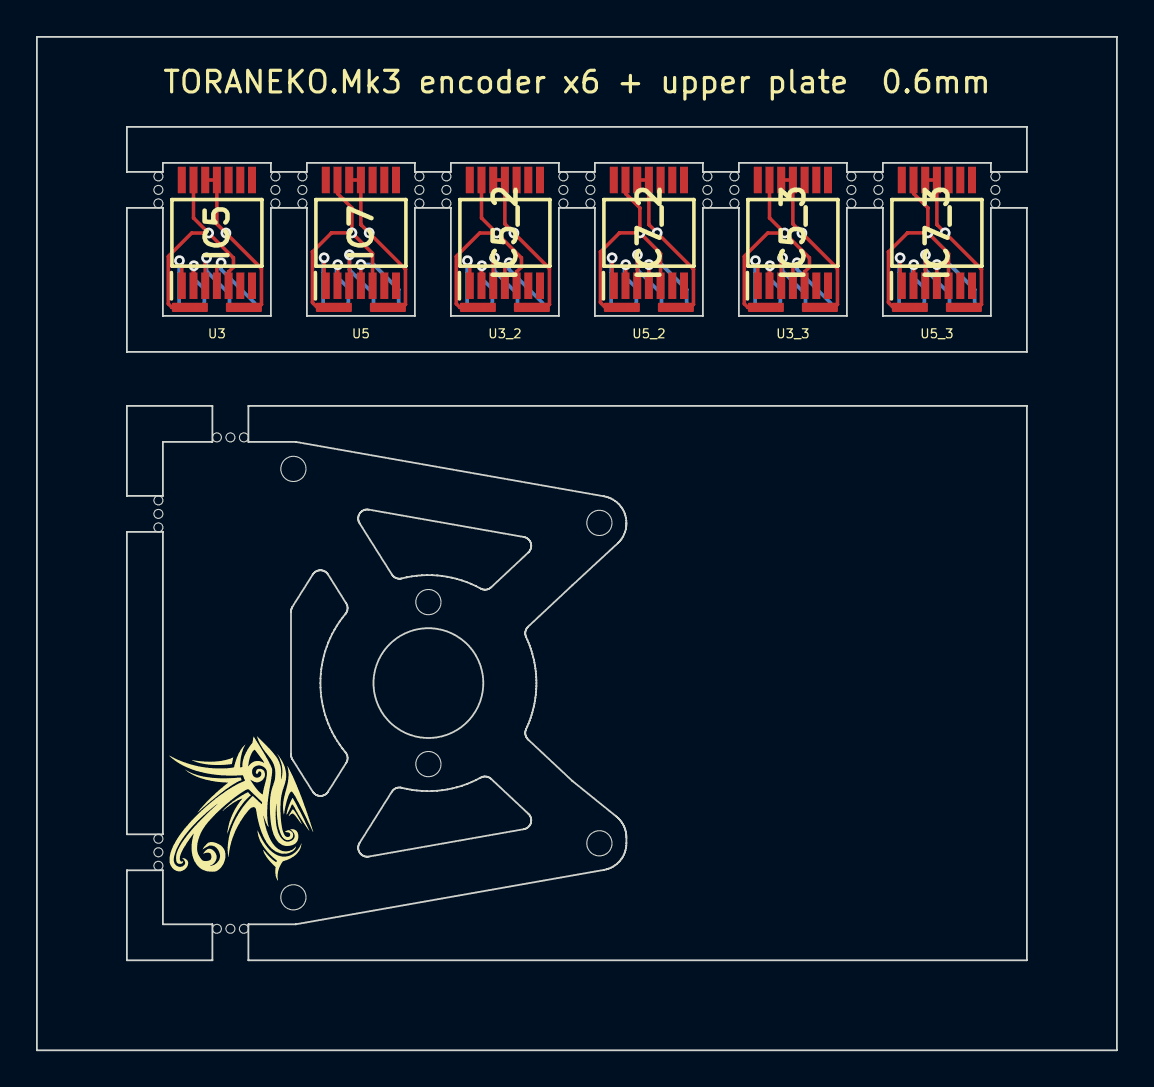
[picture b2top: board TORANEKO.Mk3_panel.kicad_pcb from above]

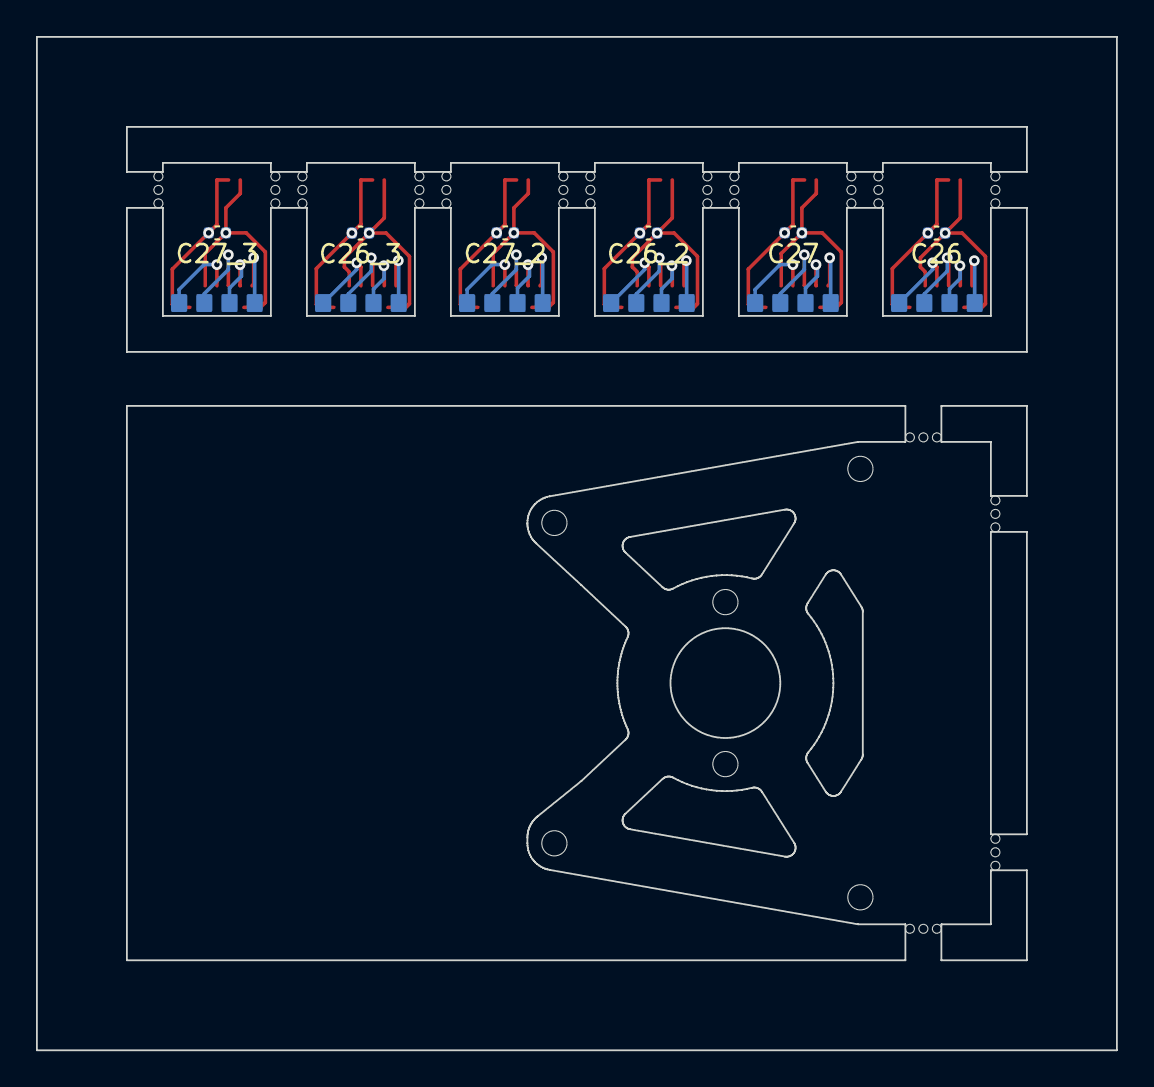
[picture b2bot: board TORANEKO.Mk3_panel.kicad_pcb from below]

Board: 2 copper layers, 60.0 x 56.3 mm, 21 parts (6 on the bottom side), 36 nets.

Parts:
C26, C26_2, C26_3, C27, C27_2, C27_3: 0.1u; C_0402_1005Metric
H101: UpperPlateHoles
IC5, IC5_2, IC5_3, IC7, IC7_2, IC7_3: AS5047P-ATSM; SOP65P640X120-14N
LOGO1: WhiteGlint; Logo
MB1: MouseBites
U3, U3_2, U3_3, U5, U5_2, U5_3: Encord; TN_ENC_Edge

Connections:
unnamed: IC5.2 (CLK), U3.3 (SCK)
unnamed: IC5_2.2 (CLK), U3_2.3 (SCK)
unnamed: IC5_3.2 (CLK), U3_3.3 (SCK)
unnamed: IC5.1 (CSN), U3.4 (CS)
unnamed: IC5_2.1 (CSN), U3_2.4 (CS)
unnamed: IC5_3.1 (CSN), U3_3.4 (CS)
unnamed: C26.1, IC5.5 (TEST), IC5.13 (GND), U3.6 (GND)
unnamed: C26_2.1, IC5_2.5 (TEST), IC5_2.13 (GND), U3_2.6 (GND)
unnamed: C26_3.1, IC5_3.5 (TEST), IC5_3.13 (GND), U3_3.6 (GND)
unnamed: IC5.3 (MISO), U3.2 (MISO)
unnamed: IC5_2.3 (MISO), U3_2.2 (MISO)
unnamed: IC5_3.3 (MISO), U3_3.2 (MISO)
unnamed: IC5.4 (MOSI), U3.1 (MOSI)
unnamed: IC5_2.4 (MOSI), U3_2.1 (MOSI)
unnamed: IC5_3.4 (MOSI), U3_3.1 (MOSI)
unnamed: C26.2, IC5.11 (VDD), IC5.12 (VDD3V), U3.5 (VCC)
unnamed: C26_2.2, IC5_2.11 (VDD), IC5_2.12 (VDD3V), U3_2.5 (VCC)
unnamed: C26_3.2, IC5_3.11 (VDD), IC5_3.12 (VDD3V), U3_3.5 (VCC)
unnamed: IC7.2 (CLK), U5.3 (SCK)
unnamed: IC7_2.2 (CLK), U5_2.3 (SCK)
unnamed: IC7_3.2 (CLK), U5_3.3 (SCK)
unnamed: IC7.1 (CSN), U5.4 (CS)
unnamed: IC7_2.1 (CSN), U5_2.4 (CS)
unnamed: IC7_3.1 (CSN), U5_3.4 (CS)
unnamed: C27.1, IC7.5 (TEST), IC7.13 (GND), U5.6 (GND)
unnamed: C27_2.1, IC7_2.5 (TEST), IC7_2.13 (GND), U5_2.6 (GND)
unnamed: C27_3.1, IC7_3.5 (TEST), IC7_3.13 (GND), U5_3.6 (GND)
unnamed: IC7.3 (MISO), U5.2 (MISO)
unnamed: IC7_2.3 (MISO), U5_2.2 (MISO)
unnamed: IC7_3.3 (MISO), U5_3.2 (MISO)
unnamed: IC7.4 (MOSI), U5.1 (MOSI)
unnamed: IC7_2.4 (MOSI), U5_2.1 (MOSI)
unnamed: IC7_3.4 (MOSI), U5_3.1 (MOSI)
unnamed: C27.2, IC7.11 (VDD), IC7.12 (VDD3V), U5.5 (VCC)
unnamed: C27_2.2, IC7_2.11 (VDD), IC7_2.12 (VDD3V), U5_2.5 (VCC)
unnamed: C27_3.2, IC7_3.11 (VDD), IC7_3.12 (VDD3V), U5_3.5 (VCC)

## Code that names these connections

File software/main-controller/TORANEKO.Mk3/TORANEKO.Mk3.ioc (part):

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Mcu.Name=STM32F411C(C-E)Ux
Mcu.Package=UFQFPN48
Mcu.UserName=STM32F411CEUx
PA0-WKUP.GPIOParameters=GPIO_Label
PA0-WKUP.GPIO_Label=LED7
PA0-WKUP.Signal=GPIO_Output
PA1.Signal=S_TIM2_CH2
PA10.GPIOParameters=GPIO_Label
PA10.GPIO_Label=LED2
PA10.Signal=GPIO_Output
PA11.GPIOParameters=GPIO_Label
PA11.GPIO_Label=LED1
PA11.Signal=GPIO_Output
PA12.GPIOParameters=GPIO_Label
PA12.GPIO_Label=SW_USER
PA12.Signal=GPIO_Input
PA13.Mode=Serial_Wire
PA13.Signal=SYS_JTMS-SWDIO
PA14.Mode=Serial_Wire
PA14.Signal=SYS_JTCK-SWCLK
PA15.GPIOParameters=GPIO_Speed,PinState,GPIO_Label
PA15.GPIO_Label=IMU_CS
PA15.GPIO_Speed=GPIO_SPEED_FREQ_HIGH
PA15.PinState=GPIO_PIN_SET
PA15.Signal=GPIO_Output
PA2.Signal=ADCx_IN2
PA3.Signal=ADCx_IN3
PA4.Signal=ADCx_IN4
PA5.Signal=ADCx_IN5
PA6.Signal=ADCx_IN6
PA7.GPIOParameters=GPIO_Label
PA7.GPIO_Label=WALL_LED_B
PA7.Signal=GPIO_Output
PA8.GPIOParameters=GPIO_Speed,PinState,GPIO_Label
PA8.GPIO_Label=ENC_L_CS
PA8.GPIO_Speed=GPIO_SPEED_FREQ_HIGH
PA8.PinState=GPIO_PIN_SET
PA8.Signal=GPIO_Output
PA9.Mode=Half_duplex(single_wire_mode)
PA9.Signal=USART1_TX
PB0.GPIOParameters=GPIO_Label
PB0.GPIO_Label=WALL_LED_A
PB0.Signal=GPIO_Output
PB1.GPIOParameters=GPIO_Label
PB1.GPIO_Label=LED6
PB1.Signal=GPIO_Output
PB10.GPIOParameters=GPIO_Label
PB10.GPIO_Label=LED4
PB10.Signal=GPIO_Output
PB12.GPIOParameters=GPIO_Label
PB12.GPIO_Label=LED3
PB12.Signal=GPIO_Output
PB13.Mode=Full_Duplex_Master
PB13.Signal=SPI2_SCK
PB14.Mode=Full_Duplex_Master
PB14.Signal=SPI2_MISO
PB15.Mode=Full_Duplex_Master
PB15.Signal=SPI2_MOSI
PB2.GPIOParameters=GPIO_Label
PB2.GPIO_Label=LED5
PB2.Signal=GPIO_Output
PB3.Mode=Full_Duplex_Master
PB3.Signal=SPI1_SCK
PB4.Mode=Full_Duplex_Master
PB4.Signal=SPI1_MISO
PB5.Mode=Full_Duplex_Master
PB5.Signal=SPI1_MOSI
PB6.Signal=S_TIM4_CH1
PB7.Signal=S_TIM4_CH2
PB8.Signal=S_TIM4_CH3
PB9.Signal=S_TIM4_CH4
PC15-OSC32_OUT.GPIOParameters=PinState,GPIO_Label
PC15-OSC32_OUT.GPIO_Label=ENC_R_CS
PC15-OSC32_OUT.PinState=GPIO_PIN_SET
PC15-OSC32_OUT.Signal=GPIO_Output
PH0\ -\ OSC_IN.Mode=HSE-External-Oscillator
PH0\ -\ OSC_IN.Signal=RCC_OSC_IN
PH1\ -\ OSC_OUT.Mode=HSE-External-Oscillator
PH1\ -\ OSC_OUT.Signal=RCC_OSC_OUT
RCC.HSE_VALUE=10000000
RCC.SYSCLKFreq_VALUE=100000000
RCC.SYSCLKSource=RCC_SYSCLKSOURCE_PLLCLK
board=custom
